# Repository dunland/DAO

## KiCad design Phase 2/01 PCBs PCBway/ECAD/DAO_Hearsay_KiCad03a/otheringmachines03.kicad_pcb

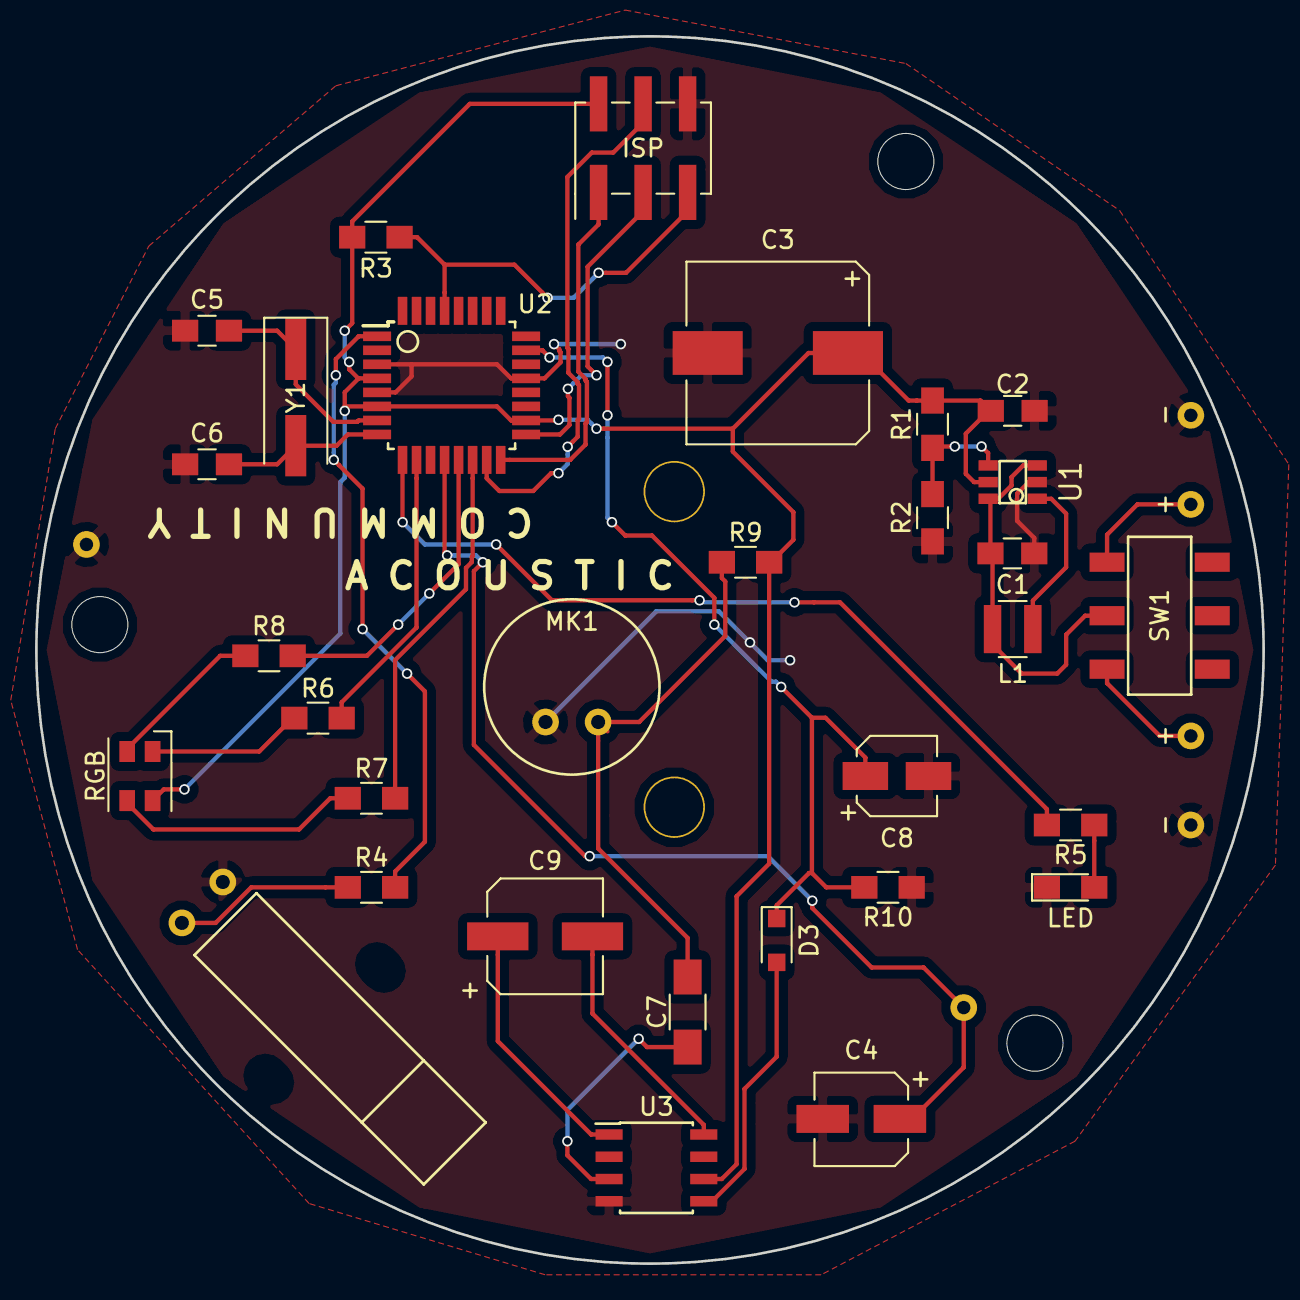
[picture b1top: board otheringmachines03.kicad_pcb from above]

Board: 2 copper layers, 70.0 x 70.0 mm, 35 parts (1 on the bottom side), 30 nets.

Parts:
BT: Batteriehalterung; Batteriehalterung_2xAA
BT1: ExtPwrSply; BatteryConnector
BT2: Battery_Cell; BatteryConnector
C1: 4.7uF; C_0805_HandSoldering
C2: 10uF; C_0805_HandSoldering
C3: 1000uF; CP_Elec_10x10.5
C4: 4.7uF; CP_Elec_5x5.3
C5, C6: 22pF; C_0805_HandSoldering
C7: 0.1uF; C_1206_HandSoldering
C8: 1uF; CP_Elec_4x5.3
C9: 22uF; CP_Elec_6.3x5.8
D1: LED; LED_0805_HandSoldering
D3: D; D_SOD-323_HandSoldering
ISP1: AVR-ISP-6; Pin_Header_Straight_2x03_Pitch2.54mm_SMD
L1: L; L_Abracon_ASPI-3012S
LS1: Speaker; SpeakerDigisoundSAL5050MC
M1: VibrationMotor; VibrationMotor17x5WithDrillHoles
MK1: Microphone; Microphone_Electret_WM52
R1: 68K; R_0805_HandSoldering
R2: 22K; R_0805_HandSoldering
R3: 10K; R_0805_HandSoldering
R4: 22; R_0805_HandSoldering
R5: 220; R_0805_HandSoldering
R6, R7: 1175; R_0805_HandSoldering
R8: 1600; R_0805_HandSoldering
R9: 30K; R_0805_HandSoldering
R10: 2.2K; R_0805_HandSoldering
RGB: LED_RAGB; LED_RCGB_AAA3528
SW1: SW_DPDT_x2; switch_SMDslide_JS202011SCQN
U1: MCP1640TIchy
U2: ATMEGA328P-AU; TQFP-32_7x7mm_Pitch0.8mm
U3: LM386; SOIC-8_3.9x4.9mm_Pitch1.27mm
Y1: 16MHz; Crystal_SMD_ABRACON_ABLS7M2

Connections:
+2V5: BT2.1, SW1.1
/5V: C2.1, C3.1, ISP1.2, R1.1, R3.1, R9.2, RGB.2, U1.5, U2.4, U2.6, U2.18, U3.6
GND: BT1.2, BT2.2, C1.2, C2.2, C3.2, C4.2, C5.2, C6.2, C8.2, D1.1, ISP1.6, LS1.2, M1.2, MK1.1, R2.2, R10.1, U1.2, U2.3, U2.5, U2.21, U3.4
unnamed: C1.1, L1.2, SW1.2, U1.3, U1.6
unnamed: C4.1, LS1.1, U2.12
unnamed: C5.1, U2.7, Y1.1
unnamed: C6.1, U2.8, Y1.2
unnamed: C7.1, U3.3
unnamed: C7.2, MK1.2, R9.1
unnamed: C8.1, D3.1, R10.2, U2.23
unnamed: C9.1, U3.1
unnamed: C9.2, U3.8
unnamed: D1.2, R5.1
unnamed: R6.1, RGB.1
unnamed: R7.1, RGB.3
unnamed: R8.1, RGB.4
unnamed: D3.2, U3.5
unnamed: ISP1.1, U2.16
unnamed: ISP1.3, U2.17
unnamed: ISP1.4, U2.15
unnamed: ISP1.5, R3.2, U2.29
unnamed: L1.1, U1.1
unnamed: M1.1, R4.1
unnamed: R1.2, R2.1, U1.4
unnamed: R4.2, U2.1
unnamed: R5.2, U2.9
unnamed: R6.2, U2.10
unnamed: R7.2, U2.14
unnamed: R8.2, U2.13
VCC: BT1.1, SW1.3

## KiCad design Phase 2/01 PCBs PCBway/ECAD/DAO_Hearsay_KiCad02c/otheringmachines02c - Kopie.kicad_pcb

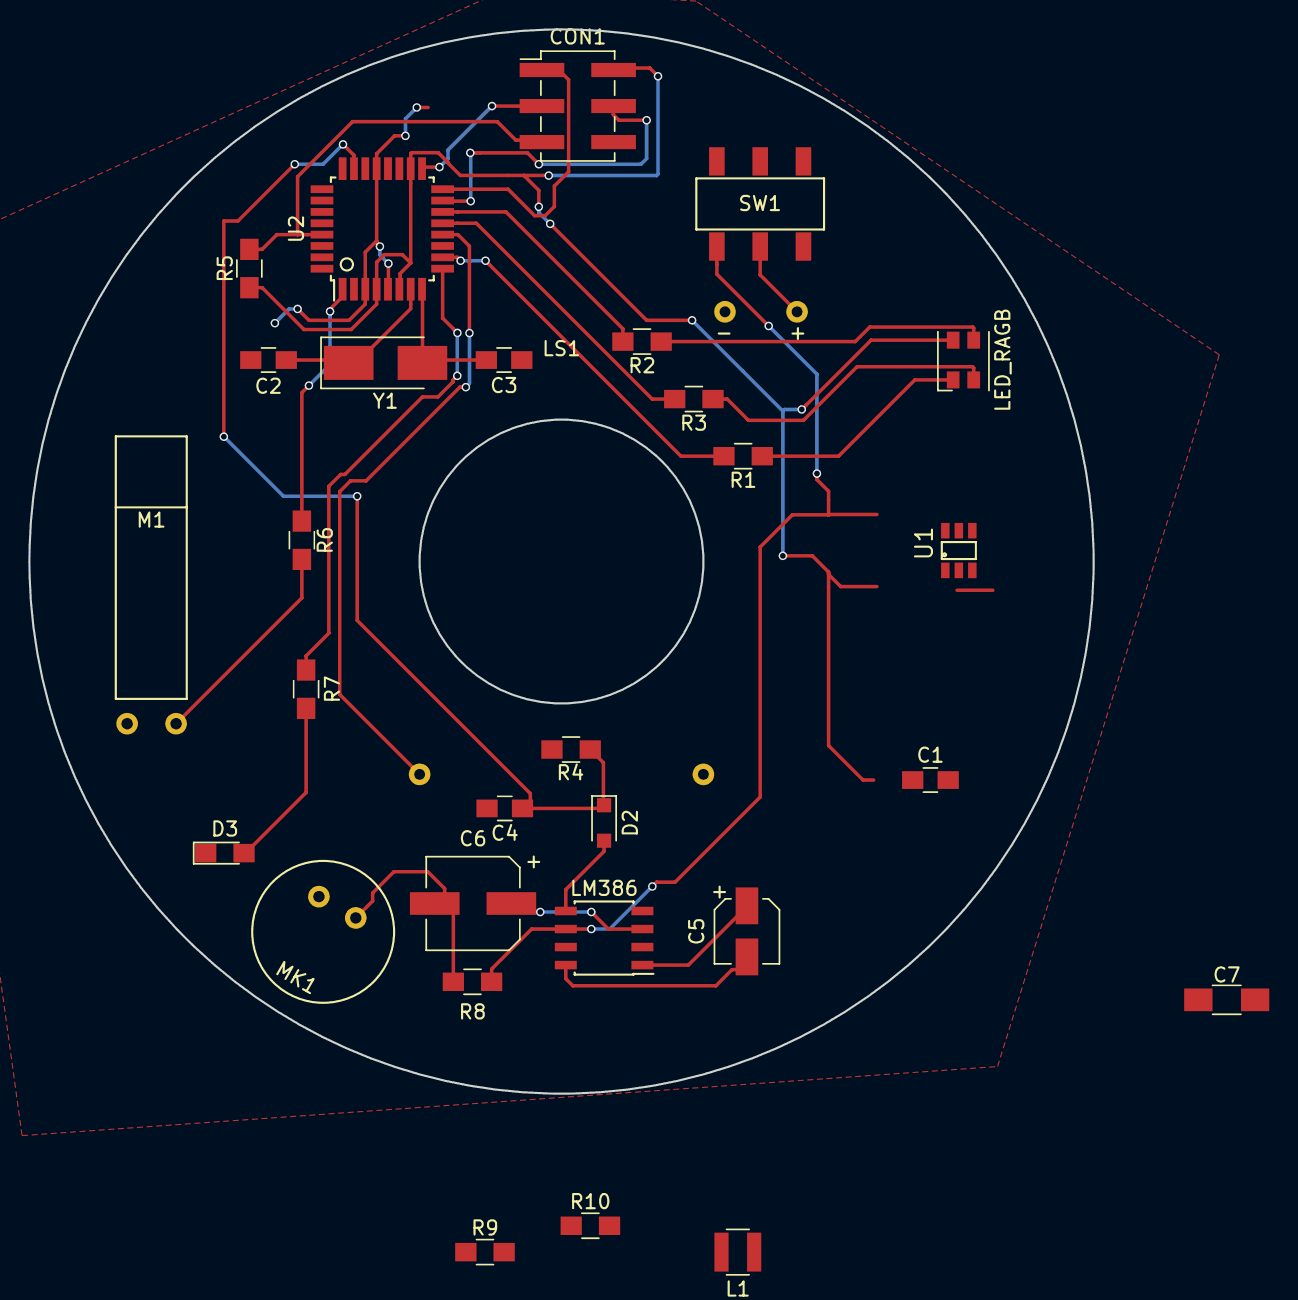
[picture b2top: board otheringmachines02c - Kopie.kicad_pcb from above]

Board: 2 copper layers, 75.0 x 75.0 mm, 31 parts (0 on the bottom side), 29 nets.

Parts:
BT1: Battery; BatteryConnector
C1: 4.7uF; C_0805_HandSoldering
C2: 10uF; C_0805_HandSoldering
C3, C4: 22pF; C_0805_HandSoldering
C5: 1uF; CP_Elec_4x5.3
C6: 22uF; CP_Elec_6.3x5.8
C7: 0.1uF; C_1206_HandSoldering
CON1: AVR-ISP-6; Pin_Header_Straight_2x03_Pitch2.54mm_SMD
D1: LED_RAGB; LED_RCGB_AAA3528
D2: D; D_SOD-323_HandSoldering
D3: LED; LED_0805_HandSoldering
L1: L; L_Abracon_ASPI-3012S
LS1: Speaker; SpeakerDigisoundSAL5050MC
M1: VibrationMotor; VibrationMotor17x5WithDrillHoles
MK1: Microphone; Microphone_Electret_WM52
R1, R2: 1175; R_0805_HandSoldering
R3: 1600; R_0805_HandSoldering
R4: 68K; R_0805_HandSoldering
R5: 22K; R_0805_HandSoldering
R6: 2.2K; R_0805_HandSoldering
R7: 10K; R_0805_HandSoldering
R8: 22; R_0805_HandSoldering
R9: 220; R_0805_HandSoldering
R10: 30K; R_0805_HandSoldering
SW1: SW_DIP_x01; switch_SMDslide_JS202011SCQN
U1: MCP1640TIchy
U2: ATMEGA328P-AU; TQFP-32_7x7mm_Pitch0.8mm
U3: LM386; SOIC-8_3.9x4.9mm_Pitch1.27mm
Y1: 16MHz; Crystal_SMD_5032-2pin_5.0x3.2mm_HandSoldering

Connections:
+2V5: BT1.1, SW1.2
/5V: C2.1, CON1.2, D1.2, R4.1, R7.1, R10.2, U1.5, U2.4, U2.6, U2.18, U3.6
GND: BT1.2, C1.2, C2.2, C3.2, C4.2, C5.2, CON1.6, D3.1, LS1.2, M1.2, MK1.2, R5.2, R6.1, U1.2, U2.3, U2.5, U2.21, U3.4
unnamed: C1.1, L1.2, SW1.1, U1.3, U1.6
unnamed: C3.1, U2.7, Y1.1
unnamed: C4.1, U2.8, Y1.2
unnamed: C5.1, D2.1, R6.2, U2.23
unnamed: C6.1, U3.1
unnamed: C6.2, U3.8
unnamed: C7.1, U3.3
unnamed: C7.2, MK1.1, R10.1
unnamed: CON1.1, U2.16
unnamed: CON1.3, U2.17
unnamed: CON1.4, U2.15
unnamed: CON1.5, R7.2, U2.29
unnamed: D1.1, R1.1
unnamed: D1.3, R2.1
unnamed: D1.4, R3.1
unnamed: D2.2, U3.5
unnamed: D3.2, R9.1
unnamed: L1.1, U1.1
unnamed: LS1.1, U2.12
unnamed: M1.1, R8.1
unnamed: R1.2, U2.10
unnamed: R2.2, U2.14
unnamed: R3.2, U2.13
unnamed: R4.2, R5.1, U1.4
unnamed: R8.2, U2.1
unnamed: R9.2, U2.9

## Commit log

2022-01-14 reupload
